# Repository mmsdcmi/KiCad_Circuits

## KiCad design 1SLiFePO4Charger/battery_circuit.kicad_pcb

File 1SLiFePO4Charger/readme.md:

Contains schematic,board and gerber files for 1S LiFePO4 charger using BQ25170 IC.

Schematic

Final PCB

Currently under fabrication.

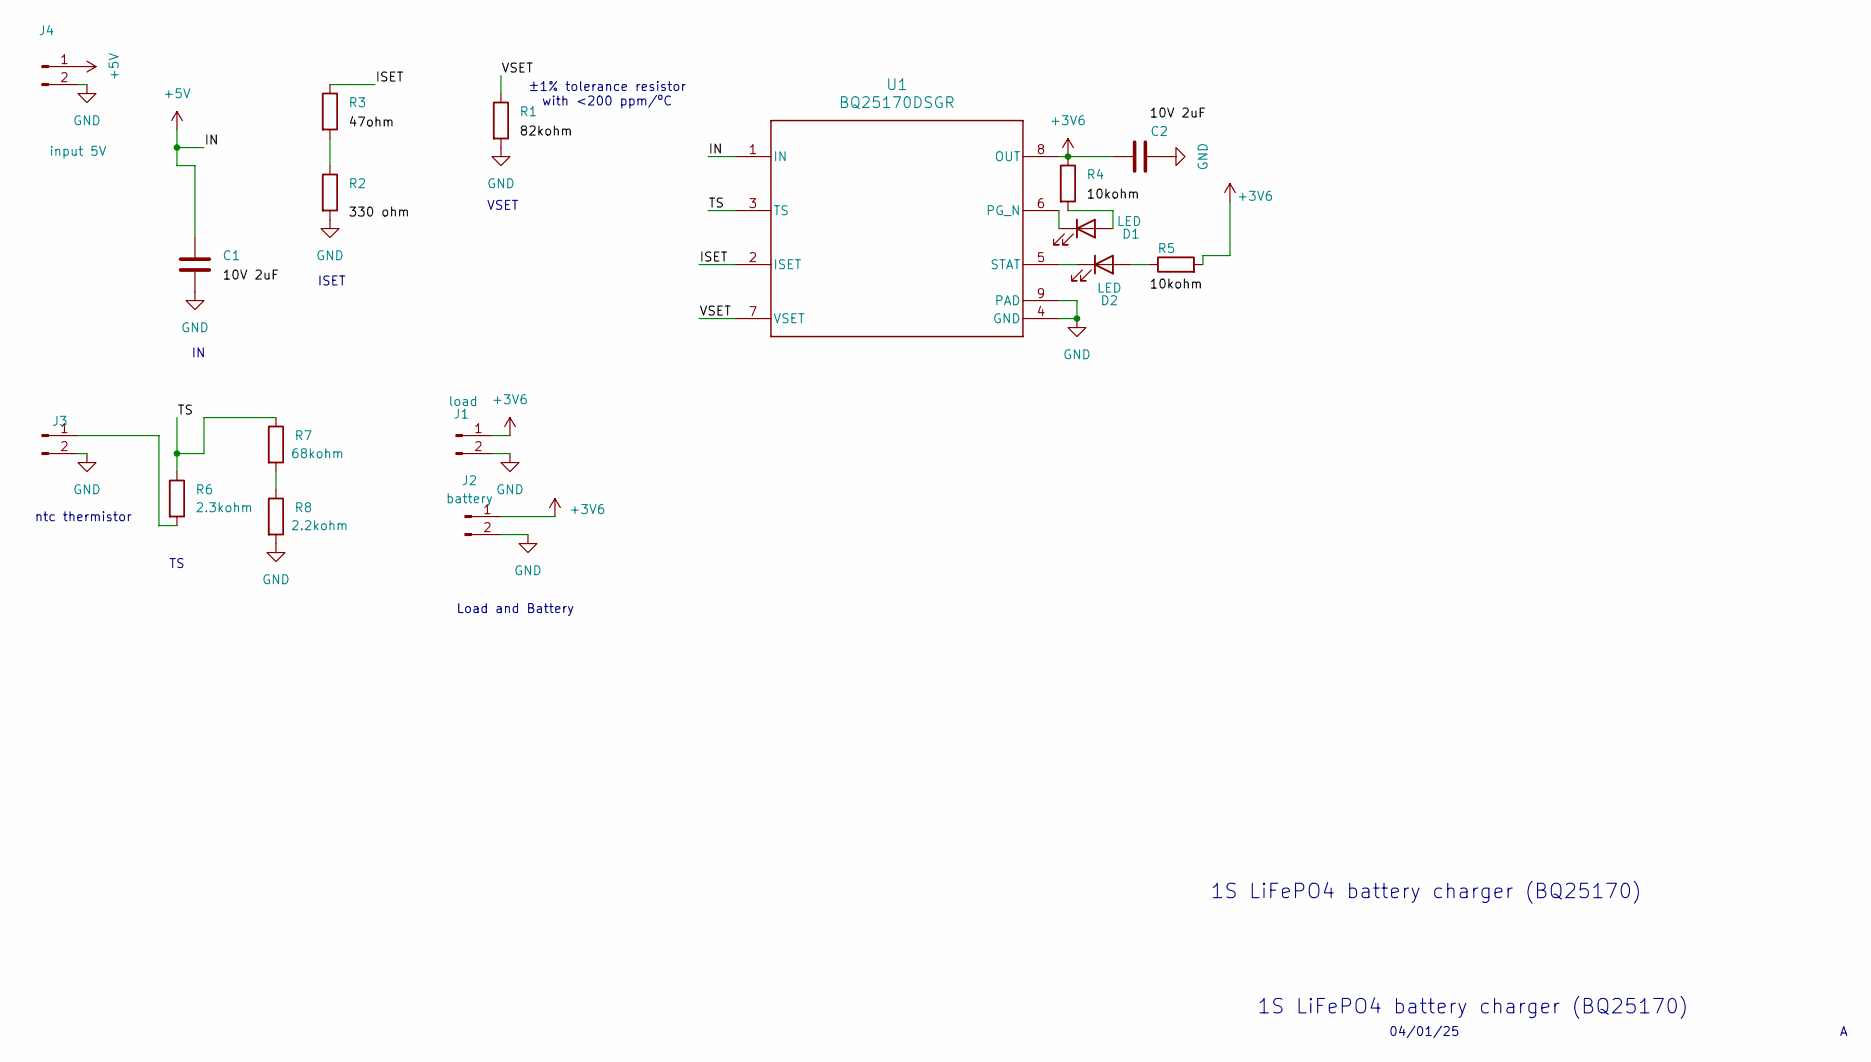
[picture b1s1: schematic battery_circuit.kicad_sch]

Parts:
C1, C2: C; C_0603_1608Metric
D1, D2: LED; LED_0805_2012Metric_Pad1.15x1.40mm_HandSolder
J1: load; PinHeader_1x02_P1.27mm_Vertical
J2: battery; PinHeader_1x02_P1.27mm_Vertical
J3, J4: input 5V; PinHeader_1x02_P1.27mm_Vertical
R1: R; R_1206_3216Metric
R2: R; R_1206_3216Metric_Pad1.30x1.75mm_HandSolder
R3: R; R_2010_5025Metric_Pad1.40x2.65mm_HandSolder
R4, R5: R; R_Axial_DIN0204_L3.6mm_D1.6mm_P2.54mm_Vertical
R6: 2.3kohm; R_0402_1005Metric_Pad0.72x0.64mm_HandSolder
R7: 68kohm; R_Axial_DIN0309_L9.0mm_D3.2mm_P12.70mm_Horizontal
R8: 2.2kohm; R_Axial_DIN0309_L9.0mm_D3.2mm_P12.70mm_Horizontal
U1: BQ25170DSGR; DSG0008A

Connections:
+3V6: C2.1, J1.1, J2.1, R4.1, R5.2, U1.8 (OUT)
+5V: C1.1, J4.1, U1.1 (IN)
/ISET: R3.1, U1.2 (ISET)
/TS: R6.1, R7.1, U1.3 (TS)
/VSET: R1.1, U1.7 (VSET)
GND: C1.2, C2.2, J1.2, J2.2, J3.2, J4.2, R1.2, R2.2, R8.2, U1.4 (GND), U1.9 (PAD)
unnamed: D1.2 (A), R4.2
unnamed: D1.1 (K), U1.6 (PG_N)
unnamed: D2.2 (A), R5.1
unnamed: D2.1 (K), U1.5 (STAT)
unnamed: J3.1, R6.2
unnamed: R2.1, R3.2
unnamed: R7.2, R8.1

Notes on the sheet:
VSET
±1% tolerance resistor with <200 ppm/ºC
04/01/25
1S LiFePO4 battery charger (BQ25170)
Load and Battery
ntc thermistor
ISET

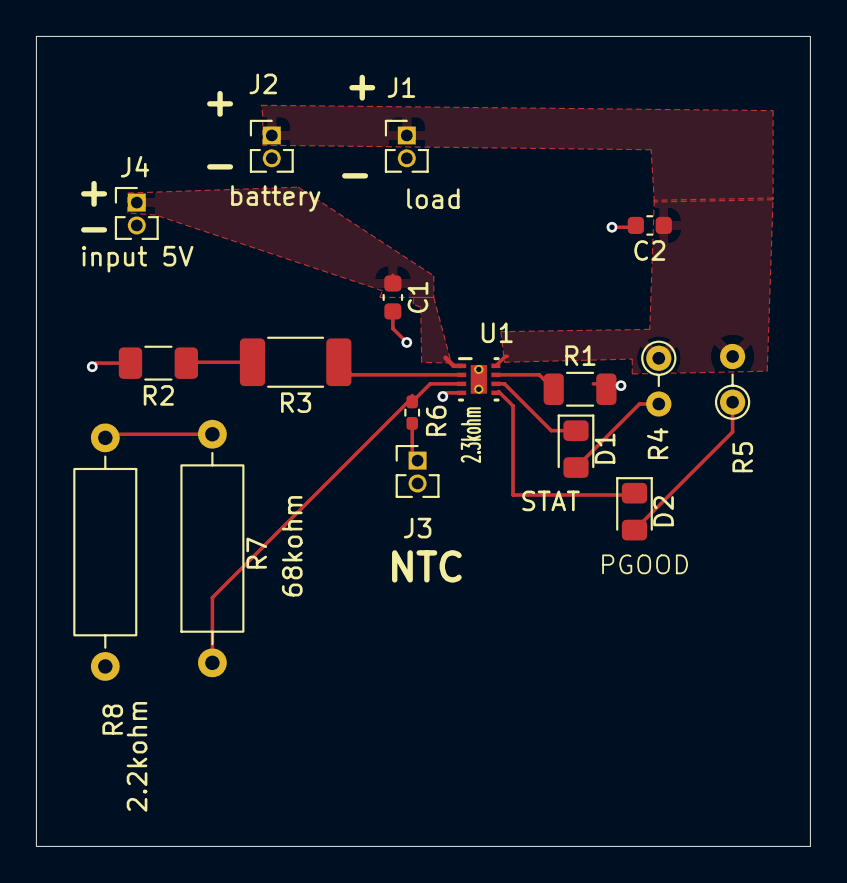
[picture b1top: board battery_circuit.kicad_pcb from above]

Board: 2 copper layers, 43.0 x 45.0 mm, 17 parts (0 on the bottom side), 13 nets.

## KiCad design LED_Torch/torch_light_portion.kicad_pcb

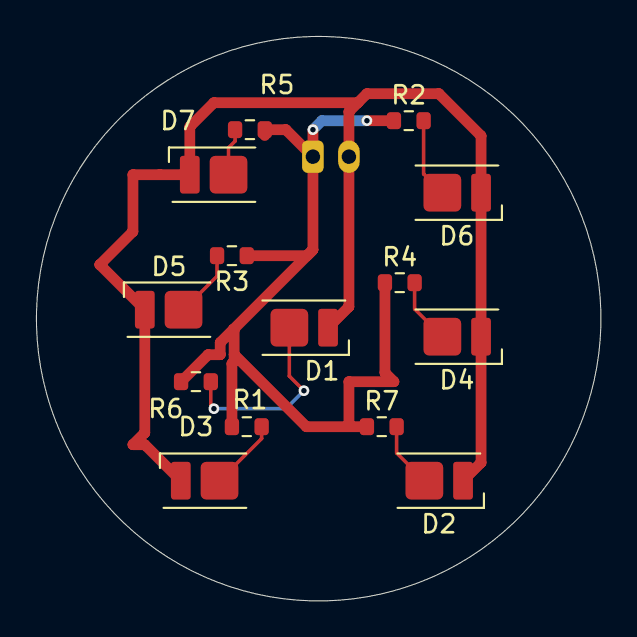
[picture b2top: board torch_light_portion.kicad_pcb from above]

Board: 2 copper layers, 31.4 x 31.4 mm, 15 parts (1 on the bottom side), 9 nets.

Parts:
D1, D2, D3, D4, D5, D6, D7: LED; LED_Everlight-SMD3528_3.5x2.8mm_67-21ST
J1: Conn_01x02_Pin; TE_440054-2_1x02_P2.00mm_Vertical
R1, R2, R3, R4, R5, R6, R7: R; R_0603_1608Metric

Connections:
+3.3V: J1.1, R1.1, R2.1, R3.1, R4.1, R5.1, R6.1, R7.1
GND: D1.1 (K), D2.1 (K), D3.1 (K), D4.1 (K), D5.1 (K), D6.1 (K), D7.1 (K), J1.2
unnamed: D1.2 (A), R6.2
unnamed: D2.2 (A), R7.2
unnamed: D3.2 (A), R1.2
unnamed: D4.2 (A), R4.2
unnamed: D5.2 (A), R3.2
unnamed: D6.2 (A), R2.2
unnamed: D7.2 (A), R5.2

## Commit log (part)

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2026-01-04 Updated files
2026-01-04 Update readme with schematic and PCB information
    Added details about the schematic and PCB for the charger.
2026-01-04 Add schematic and PCB design information to readme
    Added schematic and PCB design status to readme.
